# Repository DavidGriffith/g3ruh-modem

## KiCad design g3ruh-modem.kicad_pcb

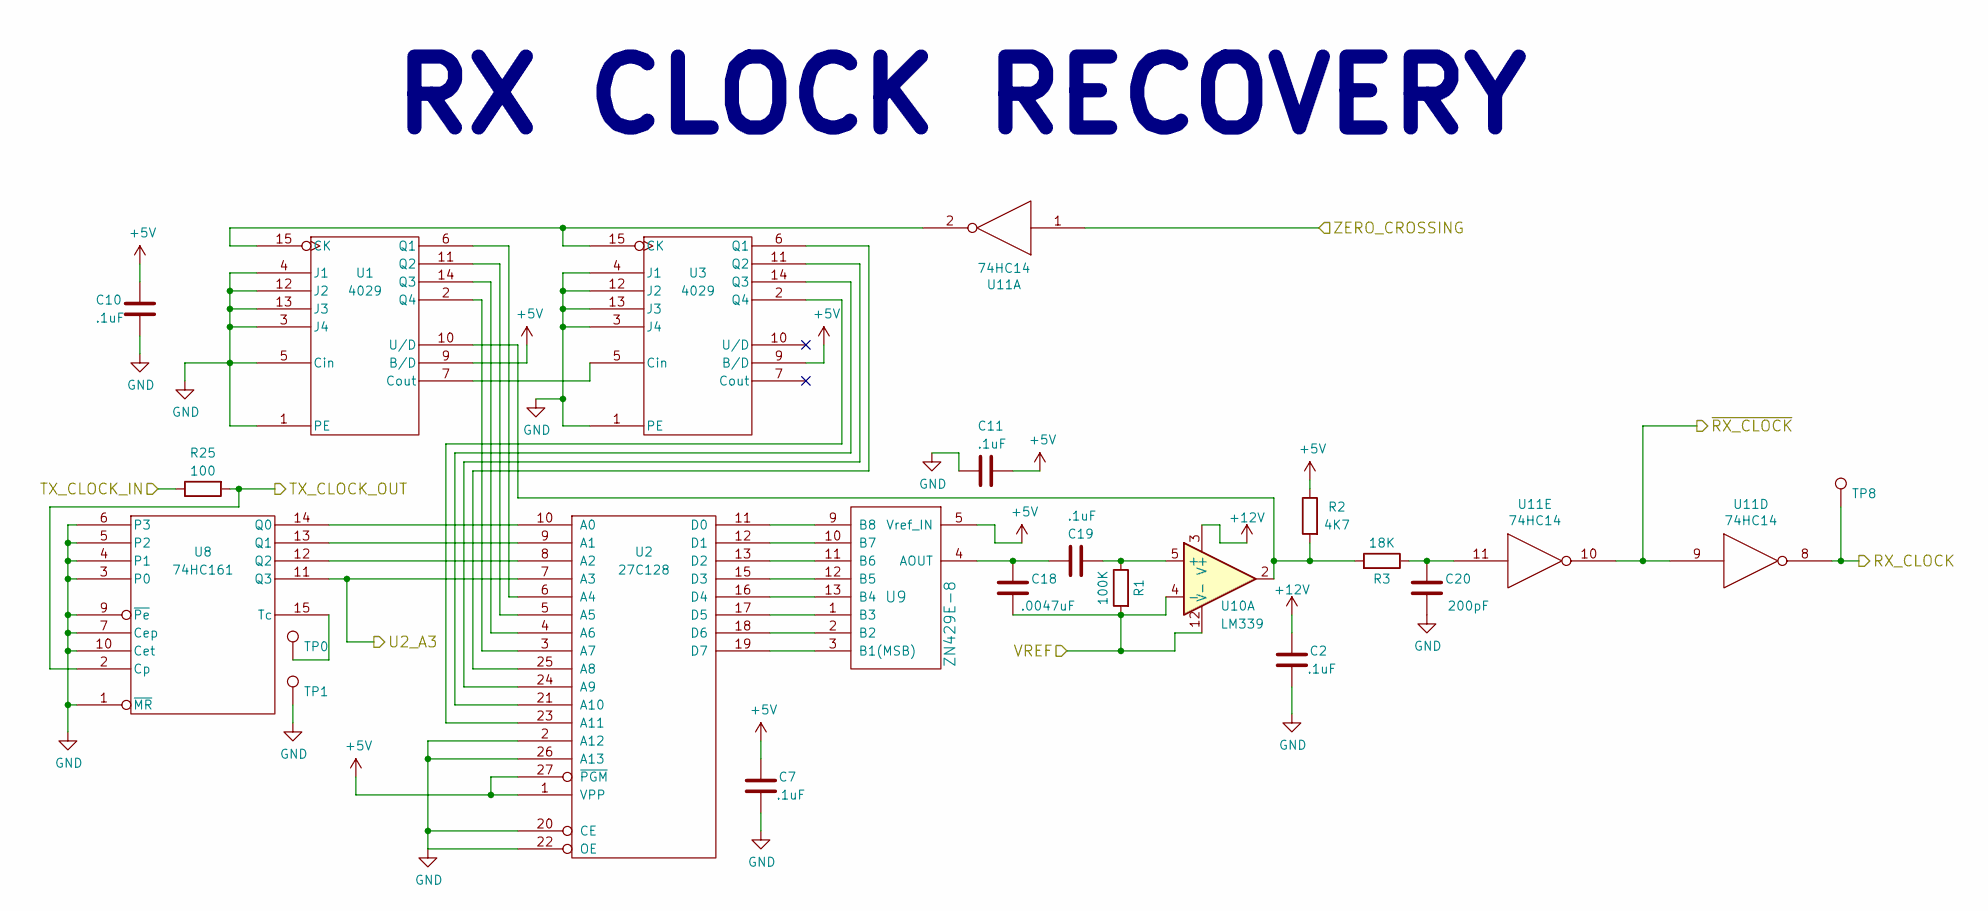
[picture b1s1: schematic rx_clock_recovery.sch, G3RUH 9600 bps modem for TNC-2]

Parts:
C2, C7, C10, C11, C19: .1uF; C_Disc_D3.0mm_W2.0mm_P2.50mm
C18: .0047uF; C_Disc_D3.0mm_W2.0mm_P2.50mm
C20: 200pF; C_Disc_D3.0mm_W2.0mm_P2.50mm
R1: 100K; R_Axial_DIN0204_L3.6mm_D1.6mm_P7.62mm_Horizontal
R2: 4K7; R_Axial_DIN0204_L3.6mm_D1.6mm_P7.62mm_Horizontal
R3: 18K; R_Axial_DIN0204_L3.6mm_D1.6mm_P7.62mm_Horizontal
R25: 100; R_Axial_DIN0204_L3.6mm_D1.6mm_P7.62mm_Horizontal
TP0, TP1, TP8: TEST_1P; PINTST
U1, U3: 4029; DIP-16_W7.62mm_Socket
U2: 27C128; DIP-28_W15.24mm
U8: 74HC161; DIP-16_W7.62mm
U9: ZN429E-8; DIP-14_W7.62mm_Socket
U10: LM339; DIP-14_W7.62mm
U11: 74HC14; DIP-14_W7.62mm

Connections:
+5V: C7.2, C10.1, C11.1, R2.1, U1.9 (B/D), U1.16 (VDD), U2.1 (VPP), U2.27 (~PGM), U2.28 (VCC), U3.9 (B/D), U3.16 (VDD), U8.16 (VCC), U9.5 (Vref_IN), U11.14 (VCC); also elsewhere on the board
+12V: C2.2, U10.3 (V+); also elsewhere on the board
/LOCK_DETECT/ZERO_CROSSING: U11.1; also elsewhere on the board
/LOCK_DETECT/~RX_CLOCK: U11.9, U11.10; also elsewhere on the board
/RX CLOCK RECOVERY/U2_A3: U2.7 (A3), U8.11 (Q3); also elsewhere on the board
/ZERO CROSSING/TX_CLOCK: R25.2, U8.2 (Cp); also elsewhere on the board
unnamed: C18.1, C19.2, U9.4 (AOUT)
unnamed: C19.1, R1.1, U10.5 (+)
unnamed: C20.1, R3.1, U11.11
unnamed: R2.2, R3.2, U1.10 (U/D), U10.2
unnamed: TP0.1, U8.15 (Tc)
unnamed: U1.2 (Q4), U2.3 (A7)
unnamed: U1.6 (Q1), U2.6 (A4)
unnamed: U1.7 (Cout), U3.5 (Cin)
unnamed: U1.11 (Q2), U2.5 (A5)
unnamed: U1.14 (Q3), U2.4 (A6)
unnamed: U1.15 (CK), U3.15 (CK), U11.2
unnamed: U2.8 (A2), U8.12 (Q2)
unnamed: U2.9 (A1), U8.13 (Q1)
unnamed: U2.10 (A0), U8.14 (Q0)
unnamed: U2.11 (D0), U9.9 (B8)
unnamed: U2.12 (D1), U9.10 (B7)
unnamed: U2.13 (D2), U9.11 (B6)
unnamed: U2.15 (D3), U9.12 (B5)
unnamed: U2.16 (D4), U9.13 (B4)
unnamed: U2.17 (D5), U9.1 (B3)
unnamed: U2.18 (D6), U9.2 (B2)
unnamed: U2.19 (D7), U9.3 (B1(MSB))
unnamed: U2.21 (A10), U3.14 (Q3)
unnamed: U2.23 (A11), U3.2 (Q4)
unnamed: U2.24 (A9), U3.11 (Q2)
unnamed: U2.25 (A8), U3.6 (Q1)
RX_CLOCK: TP8.1, U11.8; also elsewhere on the board
TX_CLOCK: R25.1; also elsewhere on the board

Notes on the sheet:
RX CLOCK RECOVERY

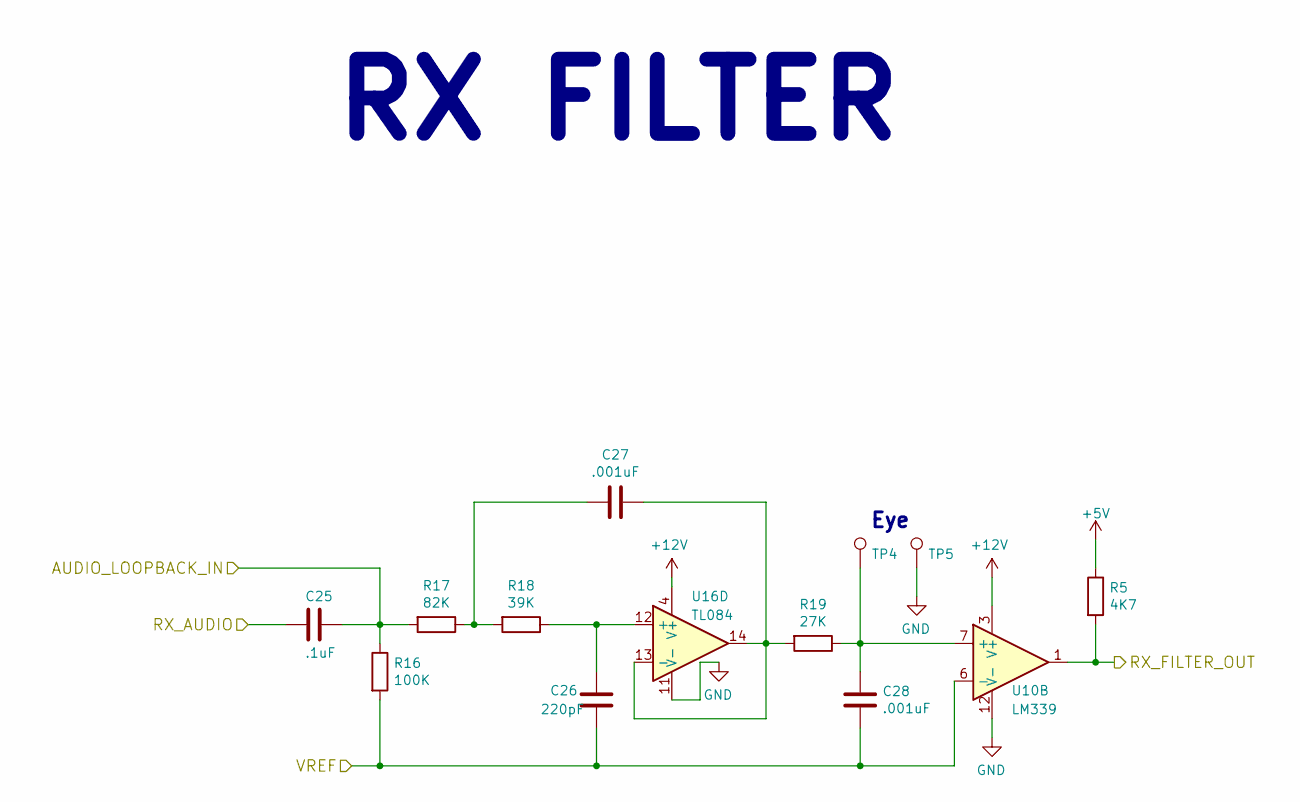
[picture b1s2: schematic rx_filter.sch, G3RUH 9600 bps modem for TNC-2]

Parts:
C25: .1uF; C_Disc_D3.0mm_W2.0mm_P2.50mm
C26: 220pF; C_Axial_L3.8mm_D2.6mm_P10.00mm_Horizontal
C27, C28: .001uF; C_Axial_L3.8mm_D2.6mm_P10.00mm_Horizontal
R5: 4K7; R_Axial_DIN0204_L3.6mm_D1.6mm_P7.62mm_Horizontal
R16: 100K; R_Axial_DIN0204_L3.6mm_D1.6mm_P7.62mm_Horizontal
R17: 82K; R_Axial_DIN0204_L3.6mm_D1.6mm_P7.62mm_Horizontal
R18: 39K; R_Axial_DIN0204_L3.6mm_D1.6mm_P7.62mm_Horizontal
R19: 27K; R_Axial_DIN0204_L3.6mm_D1.6mm_P7.62mm_Horizontal
TP4, TP5: TEST_1P; PINTST
U10: LM339; DIP-14_W7.62mm
U16: TL084; DIP-14_W7.62mm_Socket

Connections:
+5V: R5.1; also elsewhere on the board
+12V: U10.3 (V+), U16.4 (V+); also elsewhere on the board
/RX FILTER/AUDIO_LOOPBACK_IN: C25.2, R16.1, R17.2; also elsewhere on the board
/UNSCRAMBLER/RX_FILTER: R5.2, U10.1; also elsewhere on the board
unnamed: C26.1, R18.1, U16.12 (+)
unnamed: C27.1, R17.1, R18.2
unnamed: C27.2, R19.2, U16.13 (-), U16.14
unnamed: C28.1, R19.1, TP4.1, U10.7 (+)
RX_AUDIO: C25.1; also elsewhere on the board

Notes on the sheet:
Eye
RX FILTER

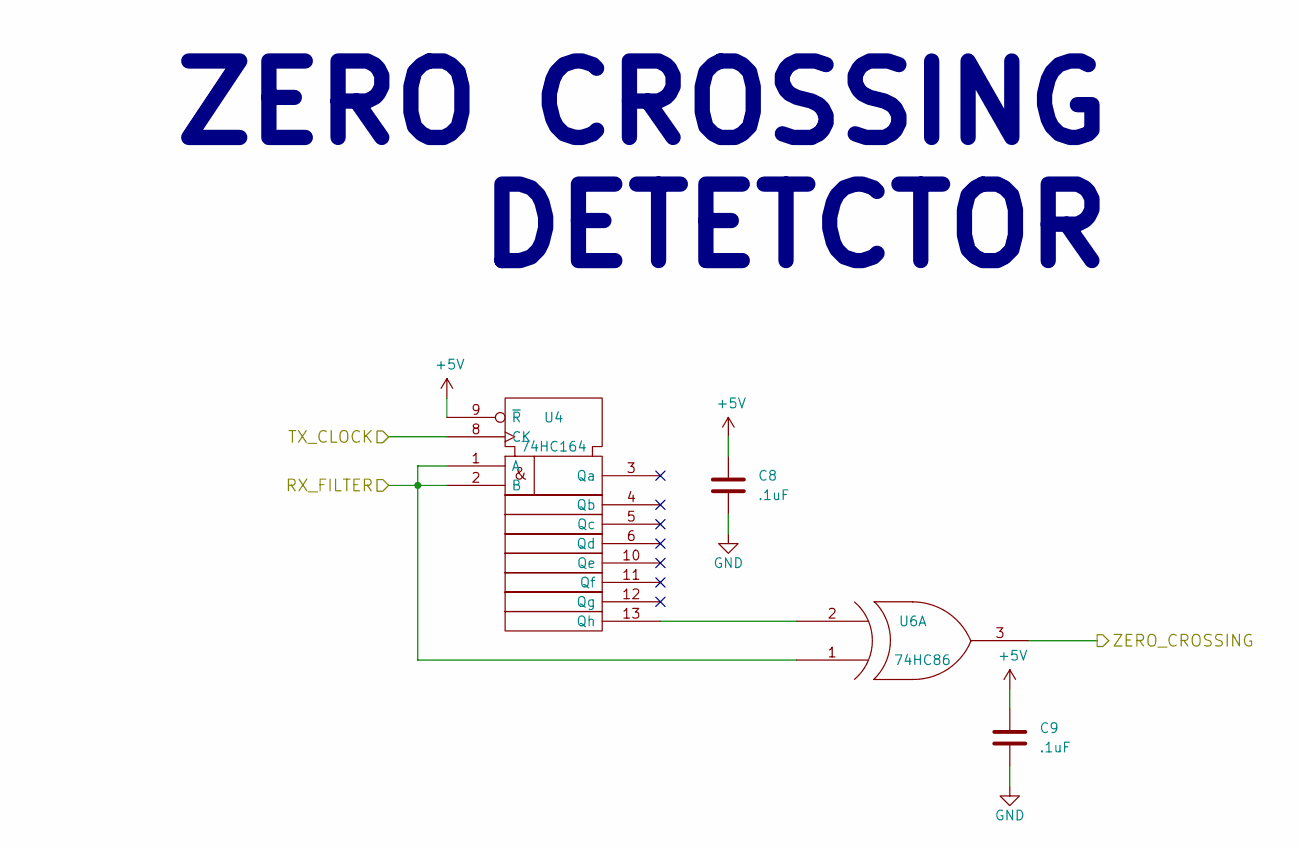
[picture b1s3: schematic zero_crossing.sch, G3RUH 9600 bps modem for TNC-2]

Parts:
C8, C9: .1uF; C_Disc_D3.0mm_W2.0mm_P2.50mm
U4: 74HC164; DIP-14_W7.62mm
U6: 74HC86; DIP-14_W7.62mm

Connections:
+5V: C8.1, C9.1, U4.9 (~R), U4.14 (Vdd), U6.14 (VCC); also elsewhere on the board
/LOCK_DETECT/ZERO_CROSSING: U6.3 (OUT); also elsewhere on the board
/UNSCRAMBLER/RX_FILTER: U4.1 (A), U4.2 (B), U6.1 (IN1); also elsewhere on the board
/ZERO CROSSING/TX_CLOCK: U4.8 (CK); also elsewhere on the board
unnamed: U4.13 (Qh), U6.2 (IN2)

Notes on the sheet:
ZERO CROSSING DETETCTOR

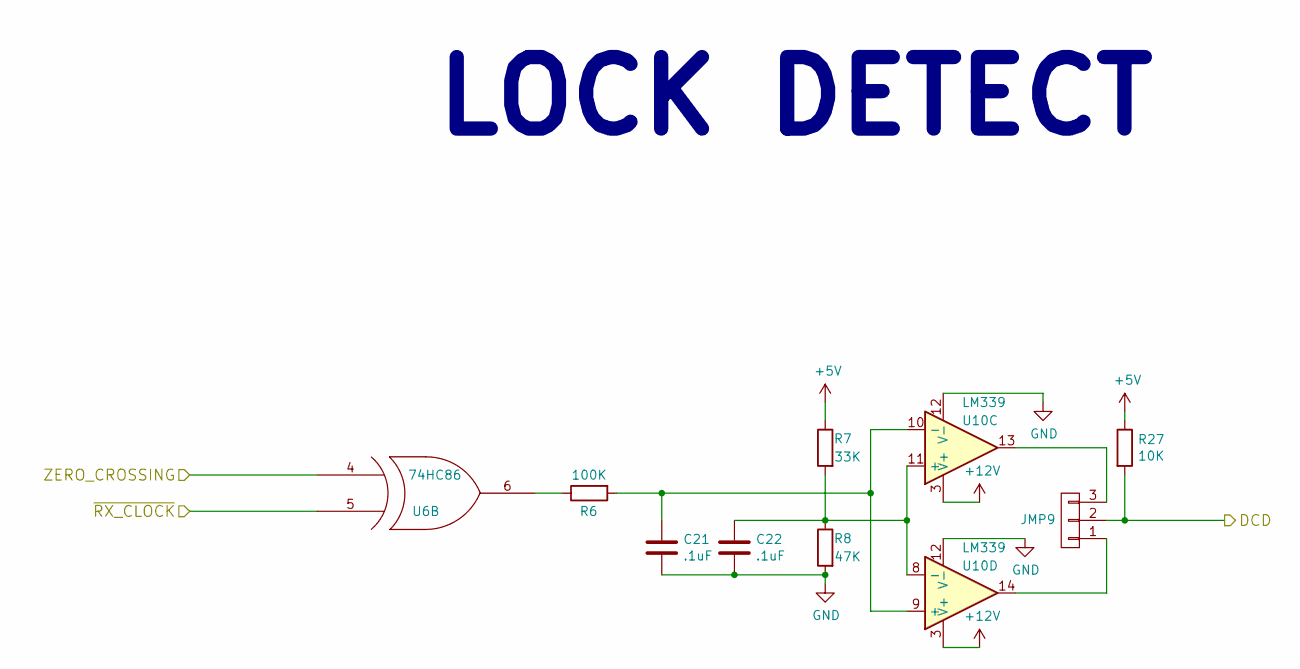
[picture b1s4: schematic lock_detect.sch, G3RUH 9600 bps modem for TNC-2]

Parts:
C21, C22: .1uF; C_Disc_D3.0mm_W2.0mm_P2.50mm
JMP9: CONN_01X03; Pin_Header_Straight_1x03_Pitch2.54mm
R6: 100K; R_Axial_DIN0204_L3.6mm_D1.6mm_P7.62mm_Horizontal
R7: 33K; R_Axial_DIN0204_L3.6mm_D1.6mm_P7.62mm_Horizontal
R8: 47K; R_Axial_DIN0204_L3.6mm_D1.6mm_P7.62mm_Horizontal
R27: 10K; R_Axial_DIN0204_L3.6mm_D1.6mm_P7.62mm_Horizontal
U6: 74HC86; DIP-14_W7.62mm
U10: LM339; DIP-14_W7.62mm

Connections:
+5V: R7.1, R27.1, U6.14 (VCC); also elsewhere on the board
+12V: U10.3 (V+); also elsewhere on the board
/LOCK_DETECT/ZERO_CROSSING: U6.4 (IN1); also elsewhere on the board
/LOCK_DETECT/~RX_CLOCK: U6.5 (IN2); also elsewhere on the board
DCD: JMP9.2, R27.2; also elsewhere on the board
unnamed: C21.1, R6.2, U10.9 (+), U10.10 (-)
unnamed: C22.1, R7.2, R8.1, U10.8 (-), U10.11 (+)
unnamed: JMP9.1, U10.14
unnamed: JMP9.3, U10.13
unnamed: R6.1, U6.6 (OUT)

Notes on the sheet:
LOCK DETECT

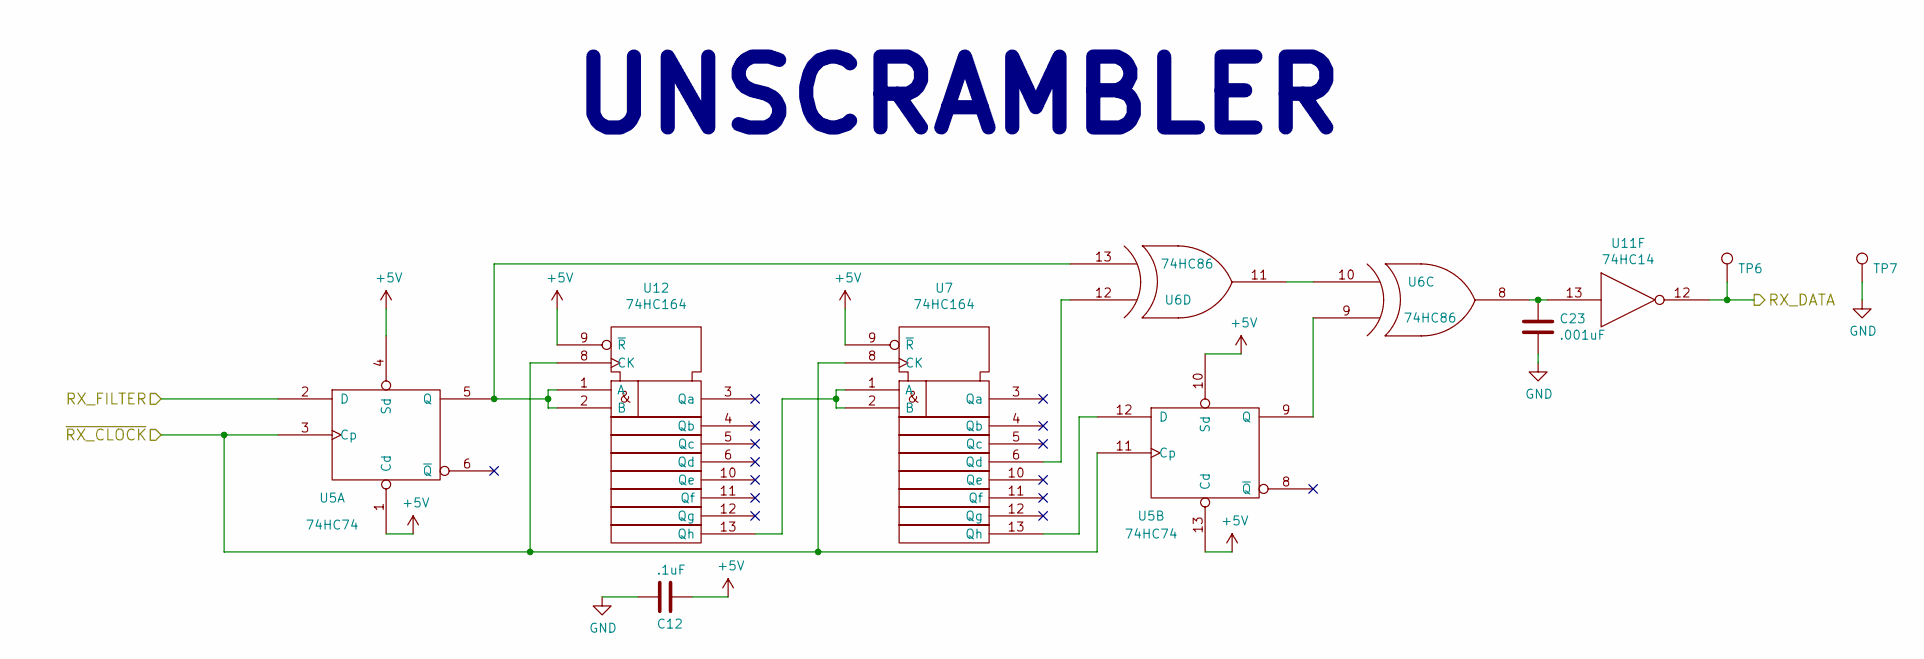
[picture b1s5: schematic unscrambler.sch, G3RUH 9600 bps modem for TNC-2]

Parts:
C12: .1uF; C_Disc_D3.0mm_W2.0mm_P2.50mm
C23: .001uF; C_Disc_D3.0mm_W2.0mm_P2.50mm
TP6, TP7: TEST_1P; PINTST
U5: 74HC74; DIP-14_W7.62mm
U6: 74HC86; DIP-14_W7.62mm
U7, U12: 74HC164; DIP-14_W7.62mm
U11: 74HC14; DIP-14_W7.62mm

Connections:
+5V: C12.1, U5.1 (Cd), U5.4 (Sd), U5.10 (Sd), U5.13 (Cd), U5.14 (VCC), U6.14 (VCC), U7.9 (~R), U7.14 (Vdd), U11.14 (VCC), U12.9 (~R), U12.14 (Vdd); also elsewhere on the board
/LOCK_DETECT/~RX_CLOCK: U5.3 (Cp), U5.11 (Cp), U7.8 (CK), U12.8 (CK); also elsewhere on the board
/UNSCRAMBLER/RX_FILTER: U5.2 (D); also elsewhere on the board
unnamed: C23.1, U6.8 (OUT), U11.13
unnamed: U5.9 (Q), U6.9 (IN1)
unnamed: U5.12 (D), U7.13 (Qh)
unnamed: U6.10 (IN2), U6.11 (OUT)
unnamed: U6.12 (IN1), U7.6 (Qd)
unnamed: U5.5 (Q), U6.13 (IN2), U12.1 (A), U12.2 (B)
unnamed: U7.1 (A), U7.2 (B), U12.13 (Qh)
RX_DATA: TP6.1, U11.12; also elsewhere on the board

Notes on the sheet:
UNSCRAMBLER

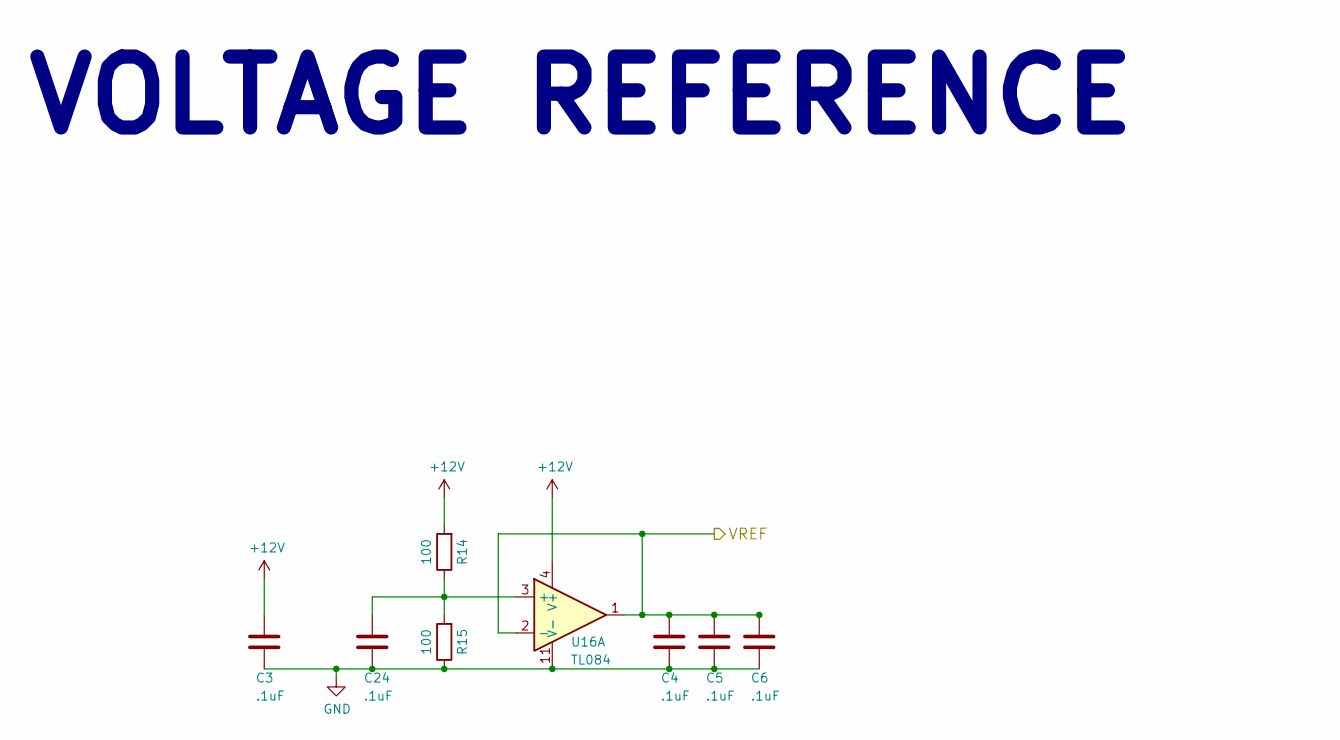
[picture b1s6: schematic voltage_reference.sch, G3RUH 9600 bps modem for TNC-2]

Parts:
C3, C4, C5, C6, C24: .1uF; C_Disc_D3.0mm_W2.0mm_P2.50mm
R14, R15: 100; R_Axial_DIN0204_L3.6mm_D1.6mm_P7.62mm_Horizontal
U16: TL084; DIP-14_W7.62mm_Socket

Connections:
+12V: C3.1, R14.2, U16.4 (V+); also elsewhere on the board
unnamed: C24.1, R14.1, R15.2, U16.3 (+)

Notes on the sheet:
VOLTAGE REFERENCE

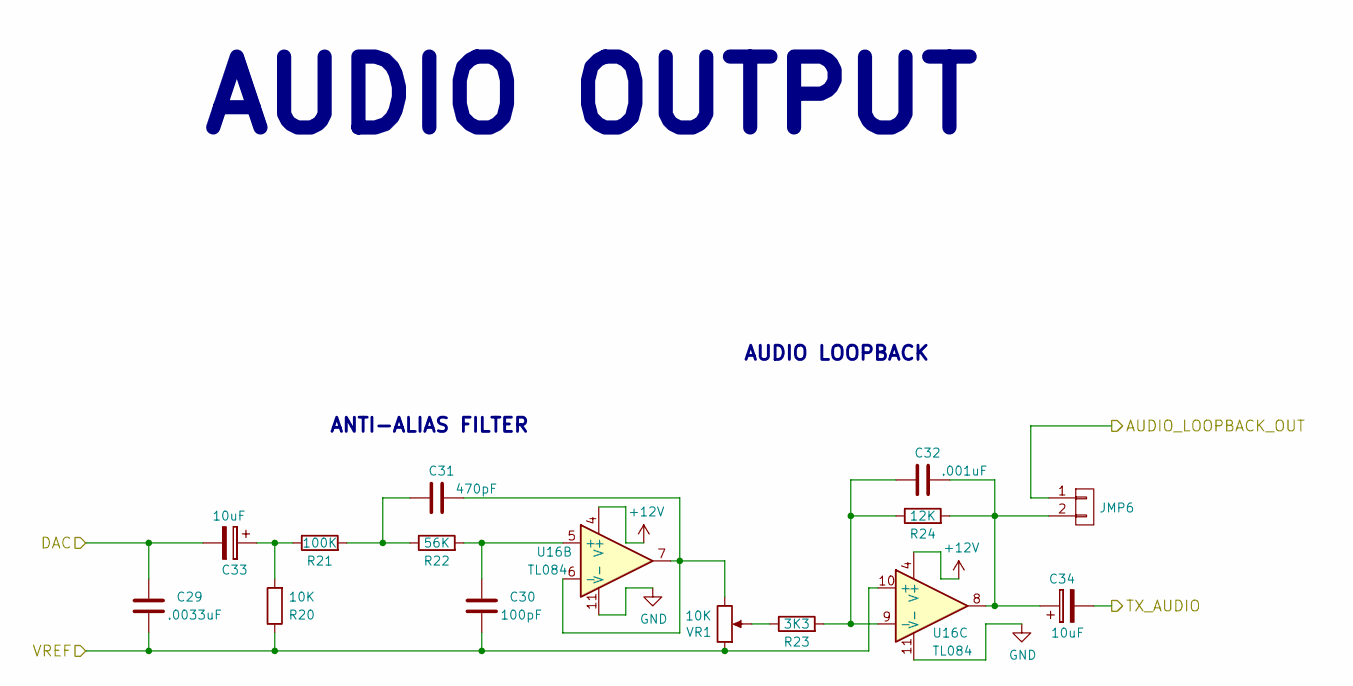
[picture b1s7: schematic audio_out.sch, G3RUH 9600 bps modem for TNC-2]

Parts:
C29: .0033uF; C_Axial_L3.8mm_D2.6mm_P10.00mm_Horizontal
C30: 100pF; C_Axial_L3.8mm_D2.6mm_P10.00mm_Horizontal
C31: 470pF; C_Axial_L3.8mm_D2.6mm_P10.00mm_Horizontal
C32: .001uF; C_Axial_L3.8mm_D2.6mm_P10.00mm_Horizontal
C33, C34: 10uF; CP_Radial_Tantal_D5.0mm_P5.00mm
JMP6: CONN_01X02; Pin_Header_Straight_1x02_Pitch2.54mm
R20: 10K; R_Axial_DIN0204_L3.6mm_D1.6mm_P7.62mm_Horizontal
R21: 100K; R_Axial_DIN0204_L3.6mm_D1.6mm_P7.62mm_Horizontal
R22: 56K; R_Axial_DIN0204_L3.6mm_D1.6mm_P7.62mm_Horizontal
R23: 3K3; R_Axial_DIN0204_L3.6mm_D1.6mm_P7.62mm_Horizontal
R24: 12K; R_Axial_DIN0204_L3.6mm_D1.6mm_P7.62mm_Horizontal
U16: TL084; DIP-14_W7.62mm_Socket
VR1: 10K; Potentiometer_Trimmer_Bourns_3296P

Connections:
+12V: U16.4 (V+); also elsewhere on the board
/AUDIO OUT/DAC: C29.1, C33.2; also elsewhere on the board
/RX FILTER/AUDIO_LOOPBACK_IN: JMP6.1; also elsewhere on the board
unnamed: C30.1, R22.2, U16.5 (+)
unnamed: C31.1, U16.6 (-), U16.7, VR1.3
unnamed: C31.2, R21.2, R22.1
unnamed: C32.1, C34.1, JMP6.2, R24.2, U16.8
unnamed: C32.2, R23.2, R24.1, U16.9 (-)
unnamed: C33.1, R20.2, R21.1
unnamed: R23.1, VR1.2
TX_AUDIO: C34.2; also elsewhere on the board

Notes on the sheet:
AUDIO LOOPBACK
ANTI-ALIAS FILTER
AUDIO OUTPUT

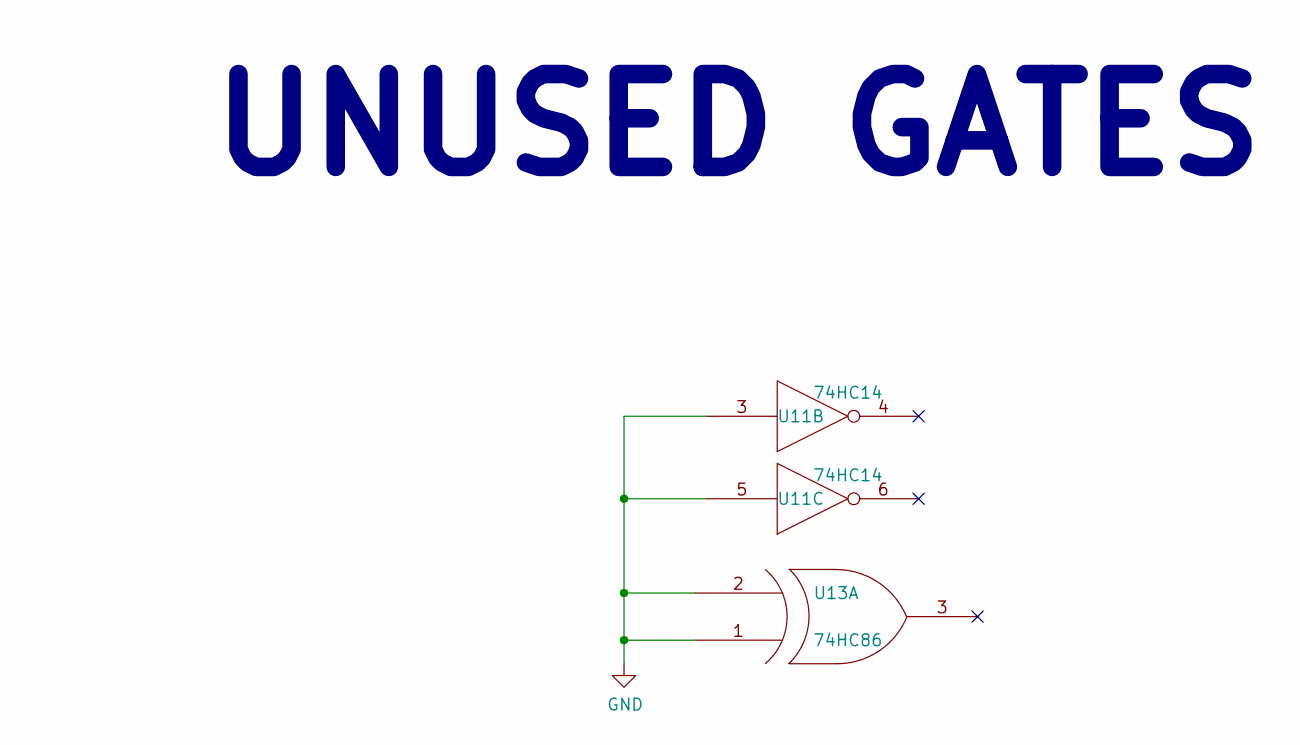
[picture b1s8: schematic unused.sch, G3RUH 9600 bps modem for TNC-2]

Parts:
U11: 74HC14; DIP-14_W7.62mm
U13: 74HC86; DIP-14_W7.62mm

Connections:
+5V: U11.14 (VCC), U13.14 (VCC); also elsewhere on the board

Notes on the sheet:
UNUSED GATES

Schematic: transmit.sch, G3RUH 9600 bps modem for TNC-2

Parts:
C14, C15, C16: .1uF; C_Disc_D3.0mm_W2.0mm_P2.50mm
JMP1, JMP2, JMP3, JMP4, JMP5: CONN_01X03; Pin_Header_Straight_1x03_Pitch2.54mm
JMP7, JMP8: CONN_01X02; Pin_Header_Straight_1x02_Pitch2.54mm
R4, R9, R10, R11, R12, R13, R28: 10K; R_Axial_DIN0204_L3.6mm_D1.6mm_P7.62mm_Horizontal
R26: 100; R_Axial_DIN0204_L3.6mm_D1.6mm_P7.62mm_Horizontal
TP2, TP3: TEST_1P; PINTST
U13: 74HC86; DIP-14_W7.62mm
U14, U18: 74HC164; DIP-14_W7.62mm
U15: 27C128; DIP-28_W15.24mm
U17: 74HC74; DIP-14_W7.62mm
U19: ZN429E-8; DIP-14_W7.62mm_Socket

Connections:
+5V: C14.1, C15.2, C16.2, R9.2, R10.2, R11.2, R12.2, R13.2, R28.2, U13.13 (IN2), U13.14 (VCC), U14.9 (~R), U14.14 (Vdd), U15.1 (VPP), U15.28 (VCC), U17.1 (Cd), U17.4 (Sd), U17.10 (Sd), U17.13 (Cd), U17.14 (VCC), U18.9 (~R), U18.14 (Vdd), U19.5 (Vref_IN); also elsewhere on the board
/AUDIO OUT/DAC: JMP7.2, R4.1; also elsewhere on the board
/RX CLOCK RECOVERY/U2_A3: U13.12 (IN1); also elsewhere on the board
unnamed: JMP1.1, U18.3 (Qa)
unnamed: JMP1.2, R10.1, U15.21 (A10)
unnamed: JMP2.1, U18.4 (Qb)
unnamed: JMP2.2, R11.1, U15.23 (A11)
unnamed: JMP3.1, U18.5 (Qc)
unnamed: JMP3.2, R12.1, U15.2 (A12)
unnamed: JMP4.1, U13.10 (IN2), U18.6 (Qd)
unnamed: JMP4.2, R13.1, U15.26 (A13)
unnamed: JMP5.1, U17.5 (Q)
unnamed: JMP5.2, R9.1, U13.4 (IN1)
unnamed: JMP7.1, U19.4 (AOUT)
unnamed: JMP8.2, R28.1, U15.27 (~PGM)
unnamed: R4.2, TP2.1
unnamed: R26.1, U17.2 (D)
unnamed: U13.5 (IN2), U13.8 (OUT)
unnamed: U13.6 (OUT), U14.1 (A), U14.2 (B)
unnamed: U13.9 (IN1), U17.9 (Q)
unnamed: U13.11 (OUT), U14.8 (CK), U17.11 (Cp), U18.8 (CK)
unnamed: U14.3 (Qa), U15.8 (A2)
unnamed: U14.4 (Qb), U15.7 (A3)
unnamed: U14.5 (Qc), U15.6 (A4)
unnamed: U14.6 (Qd), U15.5 (A5)
unnamed: U14.10 (Qe), U15.4 (A6)
unnamed: U14.11 (Qf), U15.3 (A7)
unnamed: U14.12 (Qg), U15.25 (A8)
unnamed: U14.13 (Qh), U15.24 (A9), U18.1 (A), U18.2 (B)
unnamed: U15.11 (D0), U19.9 (B8)
unnamed: U15.12 (D1), U19.10 (B7)
unnamed: U15.13 (D2), U19.11 (B6)
unnamed: U15.15 (D3), U19.12 (B5)
unnamed: U15.16 (D4), U19.13 (B4)
unnamed: U15.17 (D5), U19.1 (B3)
unnamed: U15.18 (D6), U19.2 (B2)
unnamed: U15.19 (D7), U19.3 (B1(MSB))
unnamed: U17.12 (D), U18.13 (Qh)
TX_DATA: R26.2; also elsewhere on the board

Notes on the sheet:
SCRAMBLER
TRANSMIT F.I.R.
Data / BERT
TRANSMIT

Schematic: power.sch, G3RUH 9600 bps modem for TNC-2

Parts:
C1, C13: .1uF; C_Disc_D3.0mm_W2.0mm_P2.50mm
C17: 10uF; CP_Radial_Tantal_D5.0mm_P5.00mm
D1: 1N4001; D_DO-41_SOD81_P7.62mm_Horizontal
Q1: LM7805_TO220; TO-220_Horizontal

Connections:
+5V: C13.1, C17.1, Q1.3 (VO); also elsewhere on the board
+12V: C1.1, D1.1 (K), Q1.1 (VI); also elsewhere on the board
/CONNECTORS/POWER: D1.2 (A); also elsewhere on the board

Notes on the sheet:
POWER

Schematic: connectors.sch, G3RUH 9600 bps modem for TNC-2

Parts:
P1: CONN_01X03; Pin_Header_Straight_1x03_Pitch2.54mm
P2: CONN_01X06; Pin_Header_Straight_1x06_Pitch2.54mm
P3: CONN_01X05; Pin_Header_Straight_1x05_Pitch2.54mm
P4: C96ABC; C96ABCMC

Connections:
/CONNECTORS/POWER: P1.2; also elsewhere on the board
DCD: P2.5; also elsewhere on the board
RX_AUDIO: P3.4; also elsewhere on the board
RX_CLOCK: P2.6; also elsewhere on the board
RX_DATA: P2.4; also elsewhere on the board
TX_AUDIO: P3.1; also elsewhere on the board
TX_CLOCK: P2.3; also elsewhere on the board
TX_DATA: P2.1; also elsewhere on the board

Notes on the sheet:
CONNECTORS

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
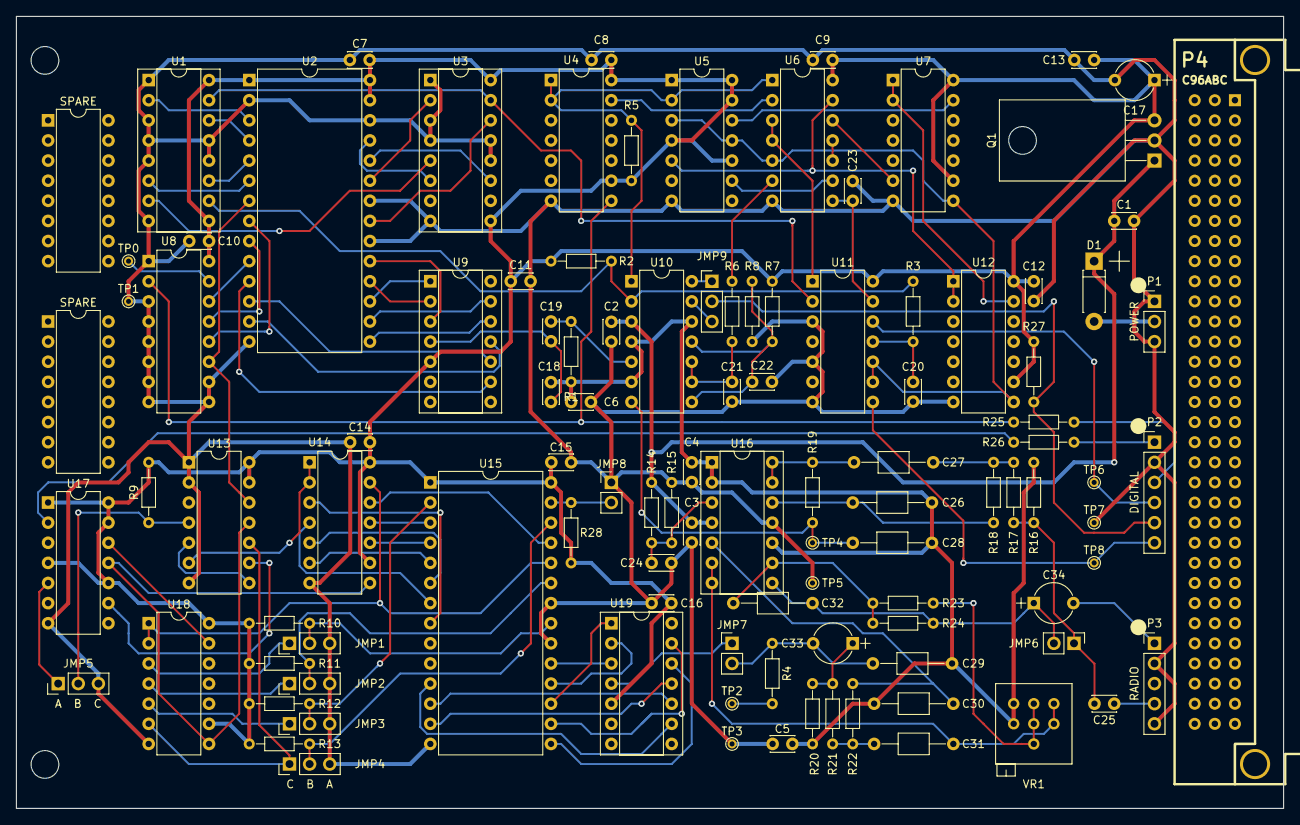
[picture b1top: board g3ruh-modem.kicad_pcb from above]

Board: 2 copper layers, 160.0 x 100.0 mm, 108 parts (0 on the bottom side), 105 nets.

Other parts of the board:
SPARE: DIP-16_W7.62mm
SPARE#2: DIP-16_W7.62mm

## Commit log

2017-07-20 Initial commit of schematics and some board fiddling.
2017-07-22 Parts in roughly the right places and footprints verified.
2017-08-08 Switched over to Kicad's hierachical sheets. There are problems.
2017-08-08 Somehow I got the connectors sheet misaligned from the 50mil grid. Passes ERC.
2017-08-09 Rearrange blocks (hierarchical sheets) for better readability.
2017-08-09 Update power.sch with project name.
2017-08-09 Final parts placement and verified net against an actual Issue 3 board.
2017-08-09 Completed routing.
2017-08-09 Fix scaling for tantalum cap 3d models.
2017-08-09 Added extra pads for pot VR1 to allow for a variety of possible parts.
2017-08-09 Added a 3D render of a populated board.
2017-08-11 Corrected transcription errors.
